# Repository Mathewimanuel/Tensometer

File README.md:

# Tensometer

Stepper-driven ball-screw tensile tester for knit fabrics with embedded conductors, plus ABS and neoprene dog-bones. Teensy 4.1 firmware (`firmware/`) and a Python PC app (`software/`), protocol 0.7 shared by hand between the two.

- `CLAUDE.md`: how Claude Code works on this repo, current status, rules for agents.
- `.claude/skills/tensometer-firmware/SKILL.md`: hardware facts, architecture, safety rules, review checklist.
- `docs/decisions.md`: dated decision log (newest first). `docs/handover.md`: project context. `docs/datasheets/`: manufacturer datasheets.
- `firmware/`: PlatformIO project. Pure logic in `lib/` with native tests, hardware drivers in `src/`.
- `software/`: PySide6 PC app, CLI, and a protocol-level fake firmware (`software/README.md`).
- GitHub issues are the work queue; labels `decision` and `hardware` need Mathew.

## Quick start

Firmware (no hardware needed):

```
pip install platformio
cd firmware
pio test -e native         # unit tests
pio run -e teensy41        # phase 1 firmware
pio run -e teensy41_sim    # phase 1 + simulated continuity module
```

PC app, against the fake firmware:

```
cd software
pip install -e ".[dev]"
pytest -v
tensometer-sim                          # serves a fake Teensy on a TCP socket
python -m tensometer.gui.app            # then connect to socket://127.0.0.1:9000
```

CI runs both: `.github/workflows/firmware.yml` (hook self-test, cppcheck, native tests, both Teensy builds with `-Werror`, memory budget) and `.github/workflows/software.yml` (ruff, pytest).

## Status

Firmware: state machine, motion planner, step ISR, homing sequencer, break-detection classifier, core safety rules, command dispatcher and comms link are implemented and natively tested. Force is fail-closed until the HX711 driver lands (#10), so this build cannot move the motor. Bench bring-up must not be trusted until reset-safe pulls are fitted (#18).

PC app: connect/HELLO with exact protocol-version check, HOME/JOG/ARM/START/STOP, live and cycle plots, per-test CSV logging, review tab.

Flashing the real machine is a manual step with the e-stop in reach; agents are blocked from uploading by `.claude/hooks/block-flash.sh`.

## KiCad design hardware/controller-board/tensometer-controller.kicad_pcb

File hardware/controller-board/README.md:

# Controller board (rev 0.4): reviewed, routed, JLCPCB-ready

Phase 1 controller PCB: Teensy 4.1 socket, TB6600 interface, HX711 cable, limits,
e-stop sense, operator panel, OLED, video-sync LED, and a keyed header for the phase 2
continuity board. **65 x 72 mm** (rev 0.2 was 125 x 88), 2 layers, 1.6 mm, 1 oz, GND
poured on both layers.

Open `tensometer-controller.kicad_pro` in KiCad 10. The files are KiCad 7 format (the
newest KiCad available in the build environment); KiCad 10 opens them and asks to save
in its own format.

| Path | What |
|---|---|
| `tensometer-controller.kicad_sch` / `-schematic.pdf` | Schematic (one A2 sheet, a net label per pin) |
| `tensometer-controller.kicad_pcb` | Routed board (rules below) |
| `jlcpcb/gerbers.zip` | Gerbers + Excellon drill (plated and non-plated holes in separate files) |
| `jlcpcb/BOM.csv`, `jlcpcb/CPL.csv` | JLCPCB assembly BOM and pick-and-place (JLC column format) |
| `renders/` | Routed copper, and the Gerbers rendered back from the zip (gerbv) |
| `tensometer.kicad_sym`, `tensometer.pretty/` | Project library: Teensy 4.1 symbol and socket footprint |
| `tools/` | `design.py` (parts, nets, LCSC numbers, MPNs) and the scripts that rebuild everything: `KRT_DIR=... bash tools/build.sh` |

## What changed in rev 0.4 (independent review + requirements pass)

| Item | Rev 0.3 | Rev 0.4 | Why |
|---|---|---|---|
| 5 V converter U1 | YLPTEC R-78E5.0-1.0, 7-36 V in | **RECOM R-78HB5.0-0.5, 9-72 V in (75 V max)**, 5 V 0.5 A, 3-pin SIP on KiCad's exact footprint | The SMBJ28A TVS only starts conducting at 31 V and clamps at up to ~45 V; a contactor-coil kick could exceed the old converter's 36 V rating. (A TRACO TSR 1-4850WI was tried first; the re-review caught that its vertical version has two extra case pins the footprint lacks.) Not stocked at LCSC: buy from Farnell/RS/Mouser and hand-solder |
| STEP/DIR pull-ups | to the Teensy's +3V3 | to **3V3_PU from U6**, a second TLV75533 on +5V | The Teensy's 3V3 is missing when it is unplugged, not yet up or switched off; STEP/DIR then sat LOW (opto ON) and gave a STEP edge at power-up/unplug, failing bring-up step 2 |
| Input bulk cap | none | **C16 100 uF 50 V** electrolytic on VIN_24 | Damps cable/contactor ringing; a ceramic alone rings |
| F1 | 0.5 A / 30 V PTC | 0.5 A / **60 V** PTC | A tripped PTC holds the full supply voltage; 30 V had no margin over 24 V + transients |
| 24 V tracks | 0.5 mm, 0.2 mm clearance | **1.0 mm** (+24V, 24V_F, VIN_24), **0.5 mm clearance** for the 24 V supply nets (+24V, 24V_F, VIN_24) and **0.3 mm** for the 24 V sense nets (24V_SW, ESTOP_RTN, OPTO_A) | Inrush, fuse-trip and TVS currents; a solder bridge or debris between 24 V and a 3.3 V signal is the failure that kills the Teensy |
| E-stop sense return | J6 pin 2 tied to board GND | **Own net ESTOP_RTN** (J6.2, U5 LED cathode, D5) | The opto now actually isolates. Swapped J6 wires only reverse-bias the LED (D5 carries ~2.4 mA through R11) instead of putting post-contactor 24 V onto GND |
| J10 expansion | Unshrouded 2x8 pins | **Keyed 2x8 box header** (C492443) + **1k in series** on all 9 analog lines (RN5, RN6, R25) + **100R** on SDA/SCL (R26, R27) | A reversed plug put +5 V on an ADC pin; the 1k limits clamp current to ~1.7 mA if the phase 2 board ever drives above 3.3 V |
| Panel buttons | Straight to Teensy pins | **1k in series** from the cable (RN1, RN2, next to J7); 10k pull-ups (RN3, RN4) and 100n at the pin | ESD / miswiring current limit on a cable that leaves the box |
| OLED J8 | 1x4 socket the module plugged into (it could not physically sit there) | **JST-PH 4 cable connector**; mount the OLED on the operator panel | PH (2.0 mm) so it cannot be mated with the HX711's JST-XH 4 by mistake |
| microSD access | J4/J5 cables rose right in front of the Teensy's card slot | Limits and sync LED moved to the right edge; only flat test pads in front of the slot | The firmware logs to SD (skill section 9) |
| Decoupling | C1 14.7 mm from U1, C4 5 mm from U3, C6 6.8 mm from U4 | C1 and C2 directly under U1's pins; C4 beside U3 pin 20; C5/C6 at U4's pins | Reviewer findings |
| Test points | none | TP1-TP7: VIN_24, +5V, +3V3, +3.3VA, ENA_N, 2x GND (bare pads, not assembled) | Bench bring-up step 2 (ENA state with the Teensy in reset) |
| Drill file | PTH and NPTH merged | Separate files | Otherwise JLC may plate the M3 holes |
| Placement rotations | SOT-23, TSSOP only | Also SMDIP-4, resistor arrays, electrolytic (see checklist below) | |
| Silkscreen | DRC ignored silk overlaps | Counted in the routed-board DRC (0 now); connector labels on the board | |
| Board | 57.5 x 72 mm | 65 x 72 mm | Two box headers and a column of cable connectors on the right; still 57% smaller than rev 0.2 |

All of it is **PROPOSED** in `docs/decisions.md`, like the earlier board choices.
Ordering this board effectively approves them, and the firmware skill (section 2.1
still describes the unbuffered wiring) must be updated when they are approved.

## Clearance under the Teensy

The Teensy sits in two 8.5 mm female headers (HC-PM254-8.5H, C41376163). With its own
2.5 mm pin spacer that puts the bottom of the Teensy PCB about **11 mm** above this
board. The tallest parts underneath are D4 (SMA, 2.4 mm max) and the 0603x4 arrays
(0.5 mm); the optional PSRAM/flash chips on the Teensy's underside hang ~1.8 mm, leaving
~7 mm. **Do not solder the Teensy flush** (straight to the board) or use low-profile
sockets: the parts under it would collide. The VUSB-VIN cut is on the Teensy's
underside; do it before plugging it in.

## Layout rules

| Item | Rule | Why |
|---|---|---|
| Signal tracks | 0.25 mm, 0.2 mm clearance | Inside JLC's standard tolerance with margin. IPC-2221 B4 (coated, up to 50 V) needs 0.13 mm |
| 24 V field nets | 0.5 mm clearance to everything for +24V, 24V_F, VIN_24 (net class Field24V); 0.3 mm for 24V_SW, ESTOP_RTN, OPTO_A (Field24VSense) | Margin against bridges/debris, see above. The sense nets carry a few mA behind R11, and 0.5 mm on all six nets would not route on this board; 0.3 mm is still above IPC-2221 B4 (0.13 mm up to 50 V) |
| Power tracks | 1.0 mm: +24V, 24V_F, VIN_24; 0.5 mm: +5V, VIN_T, GND; 0.4 mm: +3.3VA, 24V_SW, ESTOP_RTN; 0.25 mm: +3V3 | IPC-2221, 1 oz, 10 C rise: 1.0 mm ~2.5 A, 0.5 mm ~1.5 A, 0.25 mm ~0.8 A. The 5 V rail is under 0.5 A; +3V3 only feeds pull-ups, the OLED, the panel LED and phase 2 logic |
| Vias | 0.6 mm pad / 0.3 mm drill, tented | JLC standard, no surcharge |
| Via-in-pad | None | Unfilled vias wick solder |
| GND | Pour on both layers, 0.3 mm clearance, thermal reliefs (0.5 mm spokes), islands removed; stitching vias on a 5 mm grid plus a ring 1.6 mm in from the edge; a dedicated via at every two-pad SMD GND pad; stitching vias that would only tie floating pour scraps together are removed | One low-impedance ground; decoupling caps get the shortest return; no floating copper |
| Edge | Copper 0.5 mm from the board edge | |
| Fiducials | 3 (1 mm copper, 2 mm mask opening) | For the SMT line |

Tracks neck down to the pad width where they enter a small pad (a fraction of a mm).

## Phase 2 expansion (J10): how it ties in

J10 is the only link to the future continuity/routing board (firmware skill sections
2.4-2.5). Pin 1 = ADC_A0 ... pin 8 = ADC_B3 (each through 1k to Teensy pins 16, 17, 20,
21, 22, 23, 24, 25), pin 9 = V_EXC_SENSE (1k to pin 26), 10/15/16 = GND, 11/12 = I2C
SDA/SCL (via 100R; shared with the OLED, 4k7 pull-ups on this board), 13 = +3V3, 14 = +5V.

- The phase 2 board does all its own analog: precision V_EXC supply, reference
  resistors, analog switches, instrumentation amps, clamps. This board only carries the
  finished 0-3.3 V signals to the ADC pins.
- Relays (via MCP23017 + ULN2803 on the phase 2 board) are driven over the shared I2C.
  The MCP23017 must run at 3.3 V (the bus pull-ups go to +3V3).
- Power budget: +5V comes from the 0.5 A R-78HB. This board uses ~0.25 A (Teensy, opto
  drive, sync LED, HX711 LDO), leaving ~0.25 A for phase 2: relays (at most two
  energised), V_EXC regulator, amps. That is enough for signal relays, but if phase 2
  needs more it should take its own supply. Total capacitance on +5V must stay under
  100 uF (converter limit for a normal start-up); this board has ~35 uF plus the Teensy's own input capacitance. +3V3 comes from the Teensy's ~250 mA regulator, which already
  feeds pull-ups, the OLED and the panel: phase 2 should use it for logic levels only and
  make its own 3.3 V for anything else.
- No phase 2 board plugged in: the ADC pins float through 1k; the firmware treats the
  continuity module as absent (module presence check, skill section 1.2).

## Checks done

- Schematic: the netlist KiCad exports matches `design.py` exactly (68 nets, 81 parts).
- PCB: every pad carries the schematic's net; footprints linked to symbols by UUID.
- KiCad DRC on the routed board, silkscreen included, with the 0.5 mm 24 V class: **0 errors, 0 unconnected**. Left: library warnings that only appear because this machine has no global KiCad library table.
- Separate GND check: every GND pad, track, via and pour fragment is one connected copper island.
- Mask Gerber has no openings at vias (tented).
- Gerbers rendered back with gerbv: outline, copper, drills and silk as expected.
- kicad-happy (github.com/aklofas/kicad-happy) analyzers and an independent reviewer agent on rev 0.3 and again on rev 0.4 (results in `docs/decisions.md`).
- Every LCSC number checked against the JLC parts database (jlcparts snapshot; stock fetched 2026-09-15..10-28, so re-check stock when ordering). U1 (R-78HB5.0-0.5) is not stocked at LCSC: Farnell, RS and Mouser carry it.
- Not done: ERC (no CLI ERC in KiCad 7), a 3D model fit check, SPICE.

## Ordering at JLCPCB

1. PCB: upload `jlcpcb/gerbers.zip`. 2 layers, 1.6 mm, 1 oz, any colour/finish.
2. Assembly: top side. Upload `BOM.csv` and `CPL.csv`.
3. **Check every polarised part in JLC's placement preview** before paying (table below). A diode or IC rotated 180 degrees still fits its pads, so the preview is the only check. D2 backwards shorts 24 V and trips F1; U3 backwards dies.
4. Cheapest route: let JLC place only the SMD parts and hand-solder the through-hole ones (U1 and all connectors): untick those BOM lines (U1 must be bought separately anyway). Each extended part carries JLC's extended-part fee.
5. Not on the BOM: the Teensy itself; 2x 1x24 female headers for its socket (C41376163, hand-solder); the J2 mating plug (C440884); test points (bare pads).

| Part | What the preview must show (board viewed from the top, USB edge up) |
|---|---|
| D1 SS34 | Cathode band on the **right** |
| D2 SMBJ28A | Cathode band at the **bottom** (towards U3) |
| D3 LED, D4 SS14, D5 1N4148W | Cathode mark on the **left** |
| Q1 AO3400A, U4 TLV75533 | Pin 1 at the **top-left** (two pins on the left for Q1, three for U4) |
| U3 74AHCT244 | Pin 1 dot at the **top-left** |
| U5 LTV-817S | Pin 1 dot at the **top-left** (its rotation is the least certain; see `gen_fab.py`) |
| C16 electrolytic | **+** at the **bottom** |
| RN1-RN6 arrays | Not polarised, but must sit square on the 8 pads |

## Before power-up

- **Cut the Teensy's VUSB-VIN pad**; the board feeds VIN through D4.
- Bench bring-up step 2 (firmware skill section 13): with the Teensy held in reset, ENA_N (TP5) must sit at the level that keeps the TB6600 disabled.
- Known, by TB6600 design: a broken ENA wire or a dead +5 V rail leaves the driver **enabled** (no step pulses, so it holds position). The contactor/e-stop is what removes motor power.
- +5V and +3V3 leave the box unfused on J7, J9 and J10. A shorted cable takes the rail down (and with it the ENA opto, see above). Acceptable for a bench machine with an e-stop; add PTCs on the cables if that changes.
- Run the I2C bus at 100 kHz: the OLED is now on a cable and phase 2 adds more.
- JLC may want panel rails because parts sit close to the edges; check when quoting.

## Design choices awaiting Mathew's OK (docs/decisions.md)

1. 74AHCT244 buffer between Teensy and TB6600 (3.3 V vs 5 V, 10 mA pin limit, reset back-feed); 10k reset-safe pulls at its inputs (issue #18).
2. E-stop sense via LTV-817S with an isolated return: LOW = 24 V present after the contactor, HIGH = e-stop pressed or wire broken.
3. Board logic powered from 24 V **before** the contactor (J1); J6 senses the contactor output.
4. HX711 off-board on the carriage, own TLV75533 LDO.
5. Rev 0.4 changes in the table above.

## Unverified, check against datasheets

- LTV-817S land pattern: uses KiCad's `SMDIP-4_W9.53mm` (standard gull-wing DIP-4).
- R-78HB5.0-0.5: pinout 1 +Vin, 2 GND, 3 +Vout, 9-72 V in, 0.5 A, 11.5 x 8.5 x 17.5 mm (RECOM datasheet); KiCad's footprint for exactly this part. Buy the vertical (non-"L") version.
- 0603x4 arrays use KiCad's convex footprint; UNI-ROYAL 4D03 is the convex type (TODO(verify) against its datasheet).
- KF2EDGR-5.08-6P and WJ500V-5.08-2P use Phoenix footprints with the same 5.08 mm pitch; body outlines differ slightly from the silkscreen.

## Connector map

| Ref | Connector | Pins |
|---|---|---|
| J1 | 5.08 mm screw, 2 | +24 V (before contactor), 0 V |
| J2 | 5.08 mm pluggable, 6 | PUL+ PUL- DIR+ DIR- ENA+ ENA- (to TB6600; the + terminals are 5 V) |
| J3 | JST-XH 4 | 3V3A, GND, DOUT, SCK (to the HX711 module) |
| J4 / J5 | JST-XH 2 | LIM_NEAR / LIM_FAR: NC switch to GND (labelled on the board) |
| J6 | 5.08 mm screw, 2 | 24 V after the contactor, that supply's 0 V (isolated from board GND by the opto) |
| J7 | IDC 2x5 box | START, STOP, JOG+, JOG-, HOME, TARE, FAULT LED (330 R on board), 3V3, GND, GND |
| J8 | JST-PH 4 | OLED: GND, 3V3, SCL, SDA |
| J9 | JST-XH 2 | Sync LED: +5 V, LED cathode (100 R on board, ~20 mA) |
| J10 | IDC 2x8 box, keyed | Phase 2: ADC_A0-3, ADC_B0-3, V_EXC_SENSE (all via 1k), GND, I2C (via 100R), 3V3, 5V, GND, GND. The phase 2 board's cable must use the same notch-to-pin-1 convention |

## How it was routed

`tools/route_board.py` drives [KiCad Routing Tools](https://github.com/drandyhaas/KiCadRoutingTools)
(MIT, commit 6ae347ba): a GND plane on B.Cu, then every net at the widths above with
B.Cu made costly so the plane stays whole. The router writes KiCad 9 syntax; the script
converts it to KiCad 7, pours GND on F.Cu, fills, drops stitching vias where both pours
are solid (and into any walled-in pour fragment), refills with island removal, removes
stitching vias that only join floating scraps, and refills again. On a board this dense
the router's result swings with its settings, so the script retries a short list of
them until KiCad's DRC reports zero unconnected items. `tools/build.sh` fails if the
final DRC has any error.

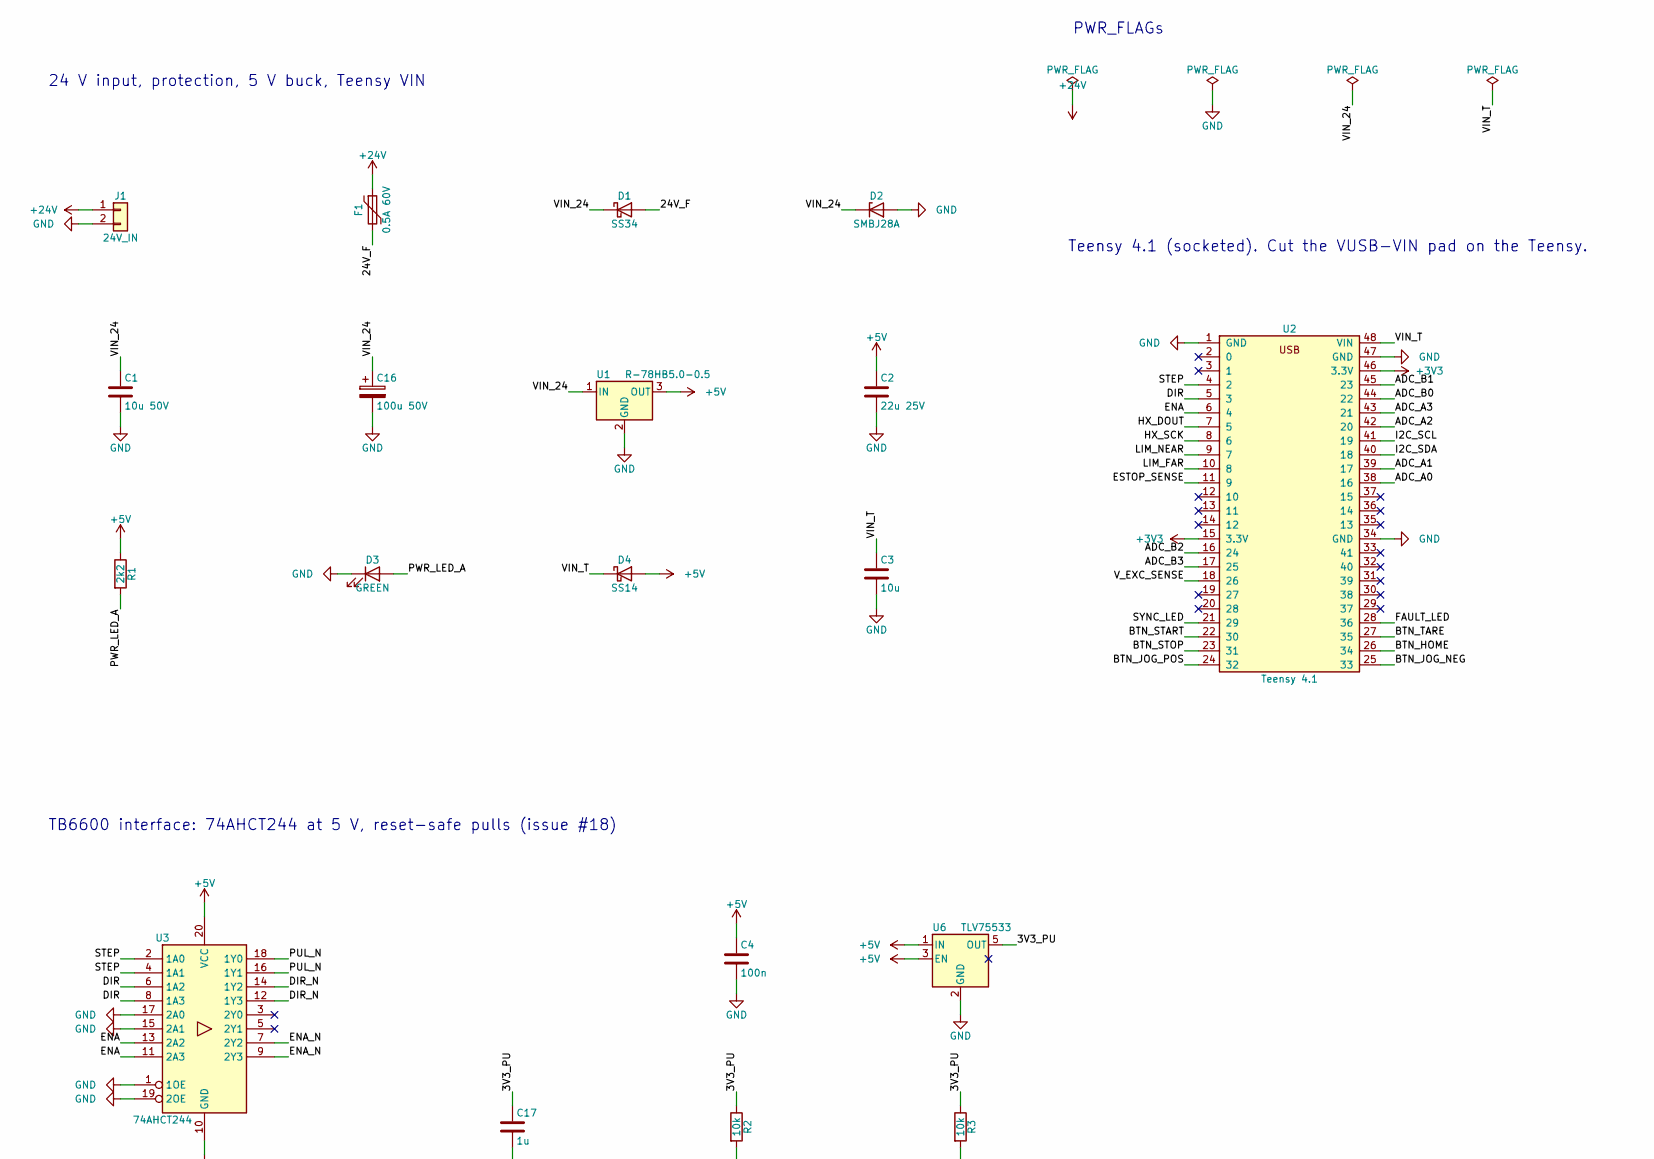
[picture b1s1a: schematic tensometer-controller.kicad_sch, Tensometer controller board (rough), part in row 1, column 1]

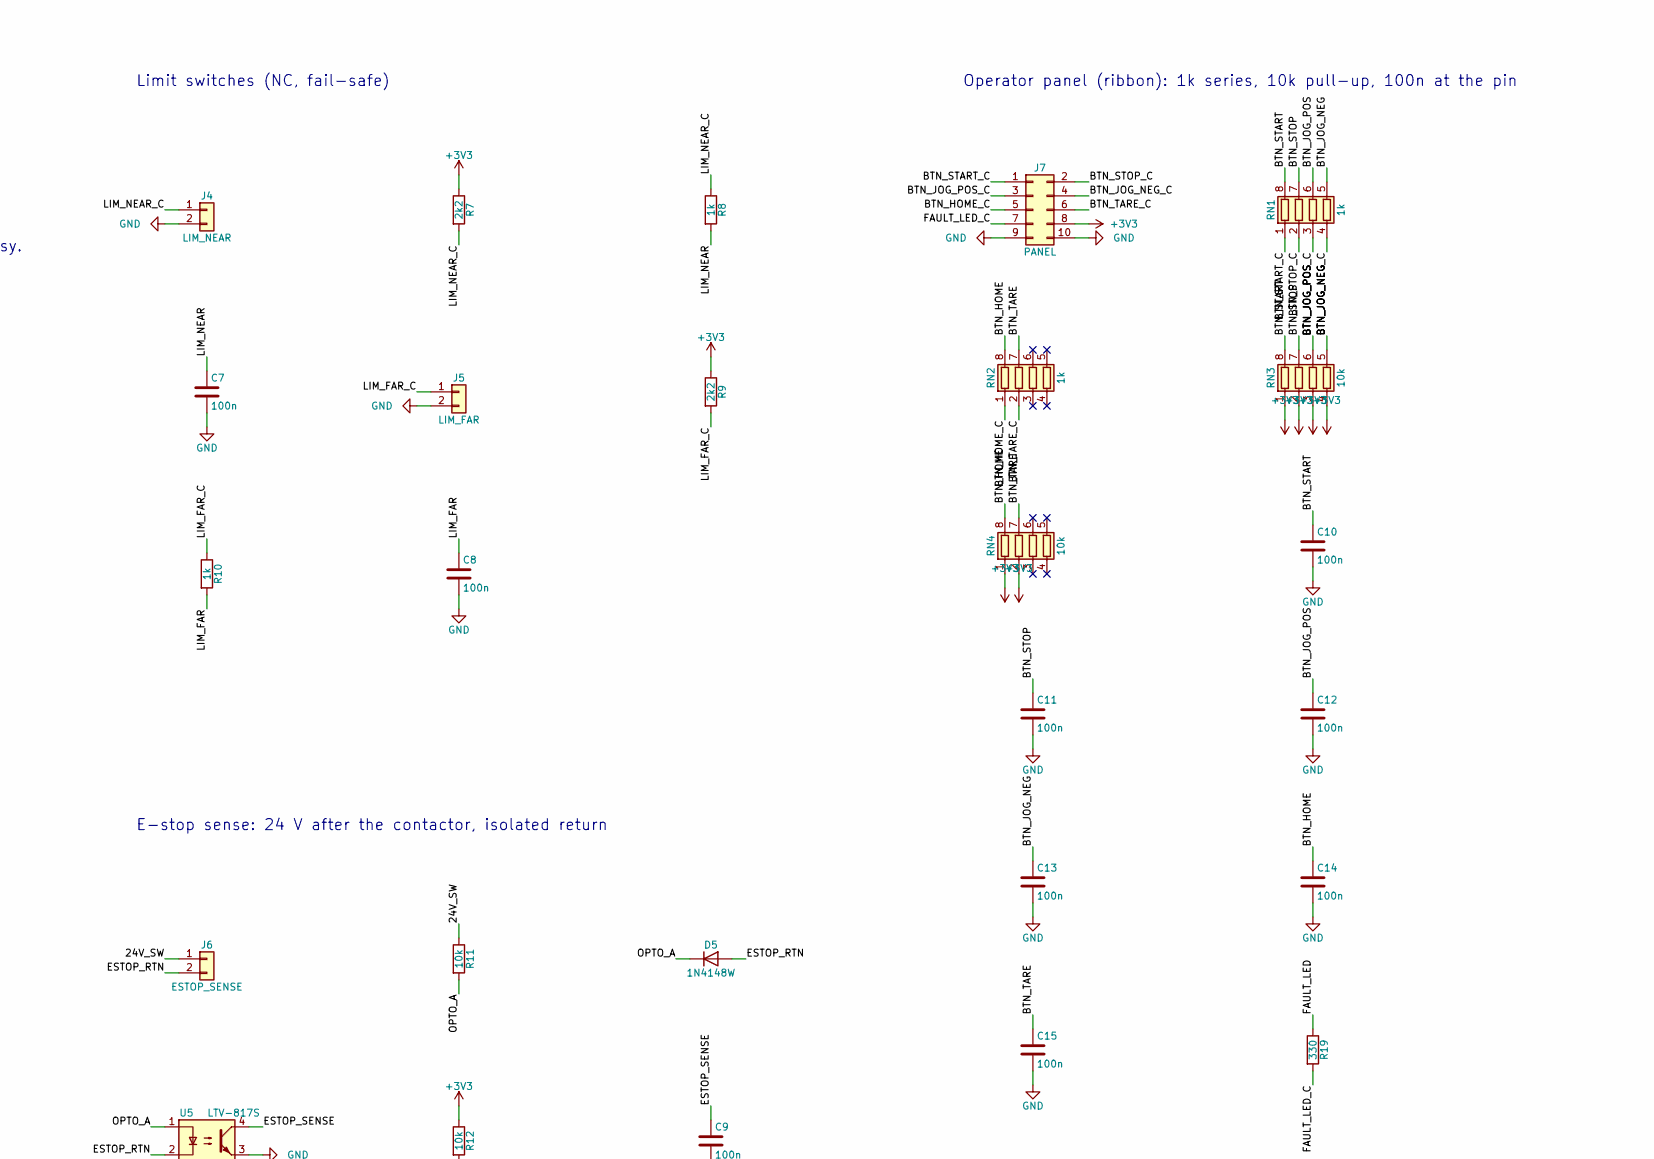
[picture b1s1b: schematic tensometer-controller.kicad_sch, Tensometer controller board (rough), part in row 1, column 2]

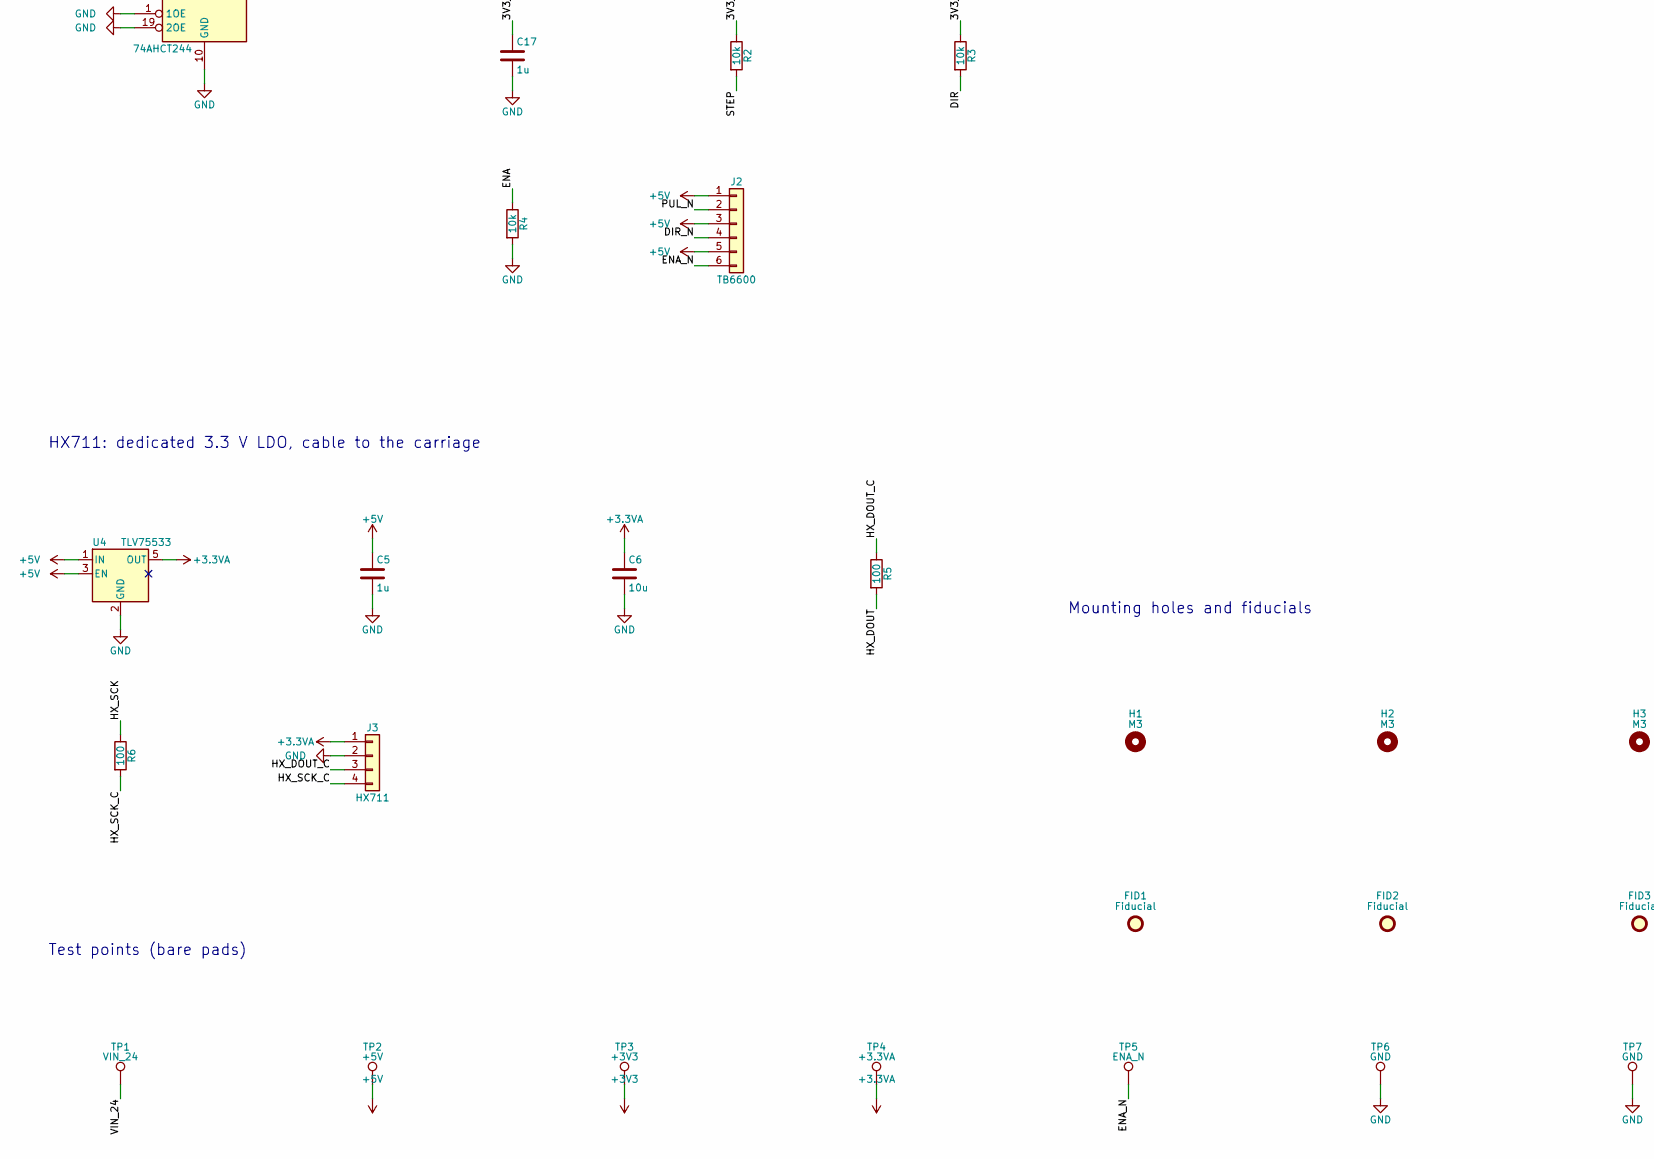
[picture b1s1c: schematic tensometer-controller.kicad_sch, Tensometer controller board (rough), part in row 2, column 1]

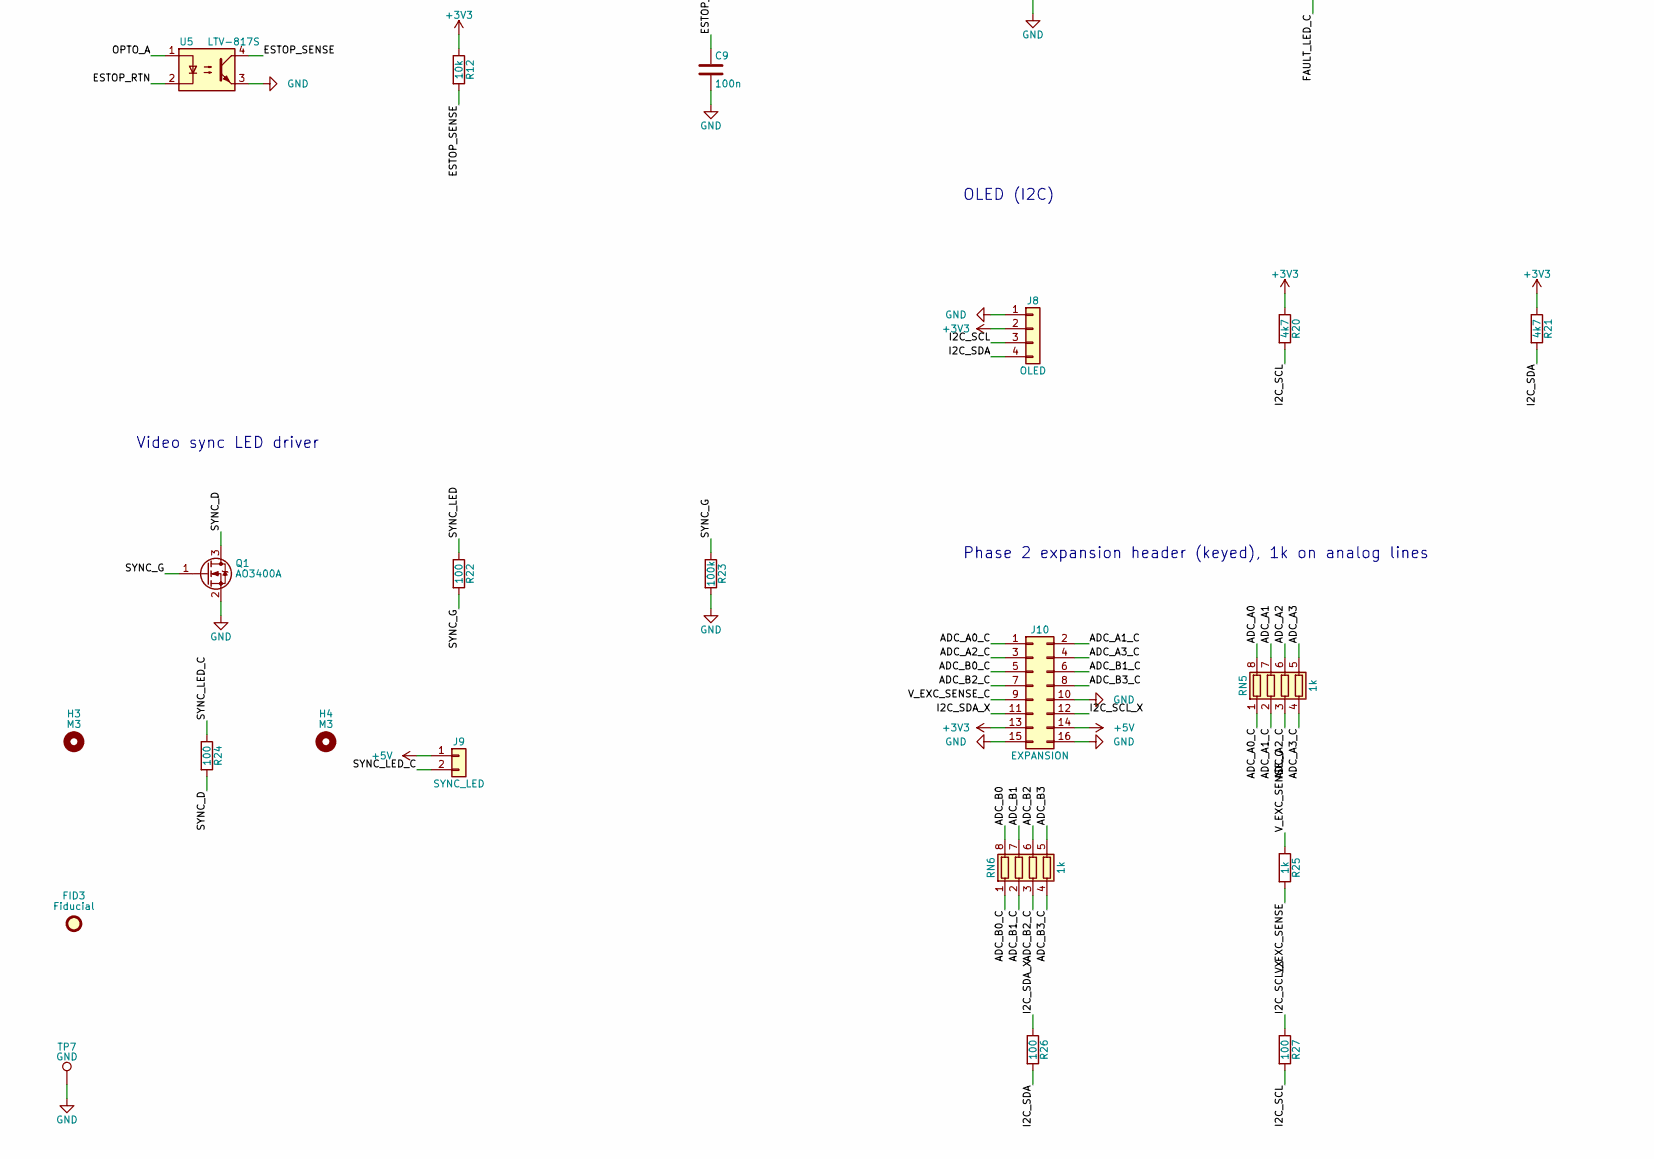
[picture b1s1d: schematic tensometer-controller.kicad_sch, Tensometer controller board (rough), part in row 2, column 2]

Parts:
C1: 10u 50V; C_1206_3216Metric; MPN CL31A106KBHNNNE; LCSC C13585
C2: 22u 25V; C_0805_2012Metric; MPN CL21A226MAQNNNE; LCSC C45783
C3, C6: 10u; C_0805_2012Metric; MPN CL21A106KAYNNNE; LCSC C15850
C4, C7, C8, C9, C10, C11, C12, C13, C14, C15: 100n; C_0805_2012Metric; MPN CC0805KRX7R9BB104; LCSC C49678
C5, C17: 1u; C_0805_2012Metric; MPN CL21B105KBFNNNE; LCSC C28323
C16: 100u 50V; CP_Elec_6.3x7.7; MPN RVT50V100M6X8; LCSC C47023117
D1: SS34; D_SMA; MPN SS34; LCSC C8678
D2: SMBJ28A; D_SMB; MPN SMBJ28A; LCSC C113997
D3: GREEN; LED_0805_2012Metric; MPN KT-0805G; LCSC C2297
D4: SS14; D_SMA; MPN SS14; LCSC C2480
D5: 1N4148W; D_SOD-123; MPN 1N4148W; LCSC C81598
F1: 0.5A 60V; Fuse_1812_4532Metric; MPN 1812L050/60GR; LCSC C19078719
FID1, FID2, FID3: Fiducial; Fiducial_1mm_Mask2mm
H1, H2, H3, H4: M3; MountingHole_3.2mm_M3
J1: 24V_IN; TerminalBlock_Phoenix_MKDS-1,5-2-5.08_1x02_P5.08mm_Horizont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; MPN WJ500V-5.08-2P; LCSC C8465
J2: TB6600; PhoenixContact_MSTBA_2,5_6-G-5,08_1x06_P5.08mm_Horizontal; MPN KF2EDGR-5.08-6P; LCSC C441208
J3: HX711; JST_XH_B4B-XH-A_1x04_P2.50mm_Vertical; MPN B4B-XH-A(LF)(SN); LCSC C144395
J4: LIM_NEAR; JST_XH_B2B-XH-A_1x02_P2.50mm_Vertical; MPN B2B-XH-A(LF)(SN); LCSC C158012
J5: LIM_FAR; JST_XH_B2B-XH-A_1x02_P2.50mm_Vertical; MPN B2B-XH-A(LF)(SN); LCSC C158012
J6: ESTOP_SENSE; TerminalBlock_Phoenix_MKDS-1,5-2-5.08_1x02_P5.08mm_Horizont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; MPN WJ500V-5.08-2P; LCSC C8465
J7: PANEL; IDC-Header_2x05_P2.54mm_Vertical; MPN 2.54-2*5P简牛; LCSC C5665
J8: OLED; JST_PH_B4B-PH-K_1x04_P2.00mm_Vertical; MPN B4B-PH-K-S(LF)(SN); LCSC C131334
J9: SYNC_LED; JST_XH_B2B-XH-A_1x02_P2.50mm_Vertical; MPN B2B-XH-A(LF)(SN); LCSC C158012
J10: EXPANSION; IDC-Header_2x08_P2.54mm_Vertical; MPN BH254V-16P; LCSC C492443
Q1: AO3400A; SOT-23; MPN AO3400A; LCSC C20917
R1, R7, R9: 2k2; R_0805_2012Metric; MPN 0805W8F2201T5E; LCSC C17520
R2, R3, R4, R12: 10k; R_0805_2012Metric; MPN 0805W8F1002T5E; LCSC C17414
R5, R6, R22, R24, R26, R27: 100; R_0805_2012Metric; MPN 0805W8F1000T5E; LCSC C17408
R8, R10, R25: 1k; R_0805_2012Metric; MPN 0805W8F1001T5E; LCSC C17513
R11: 10k; R_1206_3216Metric; MPN 1206W4F1002T5E; LCSC C17902
R19: 330; R_0805_2012Metric; MPN 0805W8F3300T5E; LCSC C17630
R20, R21: 4k7; R_0805_2012Metric; MPN 0805W8F4701T5E; LCSC C17673
R23: 100k; R_0805_2012Metric; MPN 0805W8F1003T5E; LCSC C149504
RN1, RN2, RN5, RN6: 1k; R_Array_Convex_4x0603; MPN 4D03WGJ0102T5E; LCSC C20197
RN3, RN4: 10k; R_Array_Convex_4x0603; MPN 4D03WGJ0103T5E; LCSC C29718
TP1: VIN_24; TestPoint_Pad_D1.5mm
TP2: +5V; TestPoint_Pad_D1.5mm
TP3: +3V3; TestPoint_Pad_D1.5mm
TP4: +3.3VA; TestPoint_Pad_D1.5mm
TP5: ENA_N; TestPoint_Pad_D1.5mm
TP6, TP7: GND; TestPoint_Pad_D1.5mm
U1: R-78HB5.0-0.5; Converter_DCDC_RECOM_R-78HB-0.5_THT; MPN R-78HB5.0-0.5; LCSC C7333563
U2: Teensy 4.1; Teensy41_Socket; MPN TEENSY41
U3: 74AHCT244; TSSOP-20_4.4x6.5mm_P0.65mm; MPN 74AHCT244PW,118; LCSC C135583
U4, U6: TLV75533; SOT-23-5; MPN TLV75533PDBVR; LCSC C404027
U5: LTV-817S; SMDIP-4_W9.53mm; MPN LTV-817S-TA1-C; LCSC C109227

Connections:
+3.3VA: C6.1, J3.1, TP4.1, U4.5 (OUT)
+3V3: J7.8, J8.2, J10.13, R7.1, R9.1, R12.1, R20.1, R21.1, RN3.1 (R1.1), RN3.2 (R2.1), RN3.3 (R3.1), RN3.4 (R4.1), RN4.1 (R1.1), RN4.2 (R2.1), TP3.1, U2.15 (3.3V), U2.46 (3.3V)
+5V: C2.1, C4.1, C5.1, D4.2 (A), J2.1, J2.3, J2.5, J9.1, J10.14, R1.1, TP2.1, U1.3 (OUT), U3.20 (VCC), U4.1 (IN), U4.3 (EN), U6.1 (IN), U6.3 (EN)
+24V: F1.1, J1.1
/3V3_PU: C17.1, R2.1, R3.1, U6.5 (OUT)
/24V_F: D1.2 (A), F1.2
/24V_SW: J6.1, R11.1
/ADC_A0: RN5.8 (R1.2), U2.38 (16)
/ADC_A0_C: J10.1, RN5.1 (R1.1)
/ADC_A1: RN5.7 (R2.2), U2.39 (17)
/ADC_A1_C: J10.2, RN5.2 (R2.1)
/ADC_A2: RN5.6 (R3.2), U2.42 (20)
/ADC_A2_C: J10.3, RN5.3 (R3.1)
/ADC_A3: RN5.5 (R4.2), U2.43 (21)
/ADC_A3_C: J10.4, RN5.4 (R4.1)
/ADC_B0: RN6.8 (R1.2), U2.44 (22)
/ADC_B0_C: J10.5, RN6.1 (R1.1)
/ADC_B1: RN6.7 (R2.2), U2.45 (23)
/ADC_B1_C: J10.6, RN6.2 (R2.1)
/ADC_B2: RN6.6 (R3.2), U2.16 (24)
/ADC_B2_C: J10.7, RN6.3 (R3.1)
/ADC_B3: RN6.5 (R4.2), U2.17 (25)
/ADC_B3_C: J10.8, RN6.4 (R4.1)
/BTN_HOME: C14.1, RN2.8 (R1.2), RN4.8 (R1.2), U2.26 (34)
/BTN_HOME_C: J7.5, RN2.1 (R1.1)
/BTN_JOG_NEG: C13.1, RN1.5 (R4.2), RN3.5 (R4.2), U2.25 (33)
/BTN_JOG_NEG_C: J7.4, RN1.4 (R4.1)
/BTN_JOG_POS: C12.1, RN1.6 (R3.2), RN3.6 (R3.2), U2.24 (32)
/BTN_JOG_POS_C: J7.3, RN1.3 (R3.1)
/BTN_START: C10.1, RN1.8 (R1.2), RN3.8 (R1.2), U2.22 (30)
/BTN_START_C: J7.1, RN1.1 (R1.1)
/BTN_STOP: C11.1, RN1.7 (R2.2), RN3.7 (R2.2), U2.23 (31)
/BTN_STOP_C: J7.2, RN1.2 (R2.1)
/BTN_TARE: C15.1, RN2.7 (R2.2), RN4.7 (R2.2), U2.27 (35)
/BTN_TARE_C: J7.6, RN2.2 (R2.1)
/DIR: R3.2, U2.5 (3), U3.6 (1A2), U3.8 (1A3)
/DIR_N: J2.4, U3.12 (1Y3), U3.14 (1Y2)
/ENA: R4.1, U2.6 (4), U3.11 (2A3), U3.13 (2A2)
/ENA_N: J2.6, TP5.1, U3.7 (2Y2), U3.9 (2Y3)
/ESTOP_RTN: D5.2 (A), J6.2, U5.2
/ESTOP_SENSE: C9.1, R12.2, U2.11 (9), U5.4
/FAULT_LED: R19.1, U2.28 (36)
/FAULT_LED_C: J7.7, R19.2
/HX_DOUT: R5.2, U2.7 (5)
/HX_DOUT_C: J3.3, R5.1
/HX_SCK: R6.1, U2.8 (6)
/HX_SCK_C: J3.4, R6.2
/I2C_SCL: J8.3, R20.2, R27.2, U2.41 (19)
/I2C_SCL_X: J10.12, R27.1
/I2C_SDA: J8.4, R21.2, R26.2, U2.40 (18)
/I2C_SDA_X: J10.11, R26.1
/LIM_FAR: C8.1, R10.2, U2.10 (8)
/LIM_FAR_C: J5.1, R9.2, R10.1
/LIM_NEAR: C7.1, R8.2, U2.9 (7)
/LIM_NEAR_C: J4.1, R7.2, R8.1
/OPTO_A: D5.1 (K), R11.2, U5.1
/PUL_N: J2.2, U3.16 (1Y1), U3.18 (1Y0)
/PWR_LED_A: D3.2 (A), R1.2
/STEP: R2.2, U2.4 (2), U3.2 (1A0), U3.4 (1A1)
/SYNC_D: Q1.3 (D), R24.2
/SYNC_G: Q1.1 (G), R22.2, R23.1
/SYNC_LED: R22.1, U2.21 (29)
/SYNC_LED_C: J9.2, R24.1
/VIN_24: C1.1, C16.1, D1.1 (K), D2.1 (K), TP1.1, U1.1 (IN)
/VIN_T: C3.1, D4.1 (K), U2.48 (VIN)
/V_EXC_SENSE: R25.2, U2.18 (26)
/V_EXC_SENSE_C: J10.9, R25.1
GND: C1.2, C2.2, C3.2, C4.2, C5.2, C6.2, C7.2, C8.2, C9.2, C10.2, C11.2, C12.2, C13.2, C14.2, C15.2, C16.2, C17.2, D2.2 (A), D3.1 (K), J1.2, J3.2, J4.2, J5.2, J7.9, J7.10, J8.1, J10.10, J10.15, J10.16, Q1.2 (S), R4.2, R23.2, TP6.1, TP7.1, U1.2 (GND), U2.1 (GND), U2.34 (GND), U2.47 (GND), U3.1 (1OE), U3.10 (GND), U3.15 (2A1), U3.17 (2A0), U3.19 (2OE), U4.2 (GND), U5.3, U6.2 (GND)

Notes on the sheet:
24 V input, protection, 5 V buck, Teensy VIN
Teensy 4.1 (socketed). Cut the VUSB-VIN pad on the Teensy.
TB6600 interface: 74AHCT244 at 5 V, reset-safe pulls (issue #18)
HX711: dedicated 3.3 V LDO, cable to the carriage
Limit switches (NC, fail-safe)
E-stop sense: 24 V after the contactor, isolated return
Operator panel (ribbon): 1k series, 10k pull-up, 100n at the pin
OLED (I2C)
Video sync LED driver
Phase 2 expansion header (keyed), 1k on analog lines
Test points (bare pads)
Mounting holes and fiducials
PWR_FLAGs

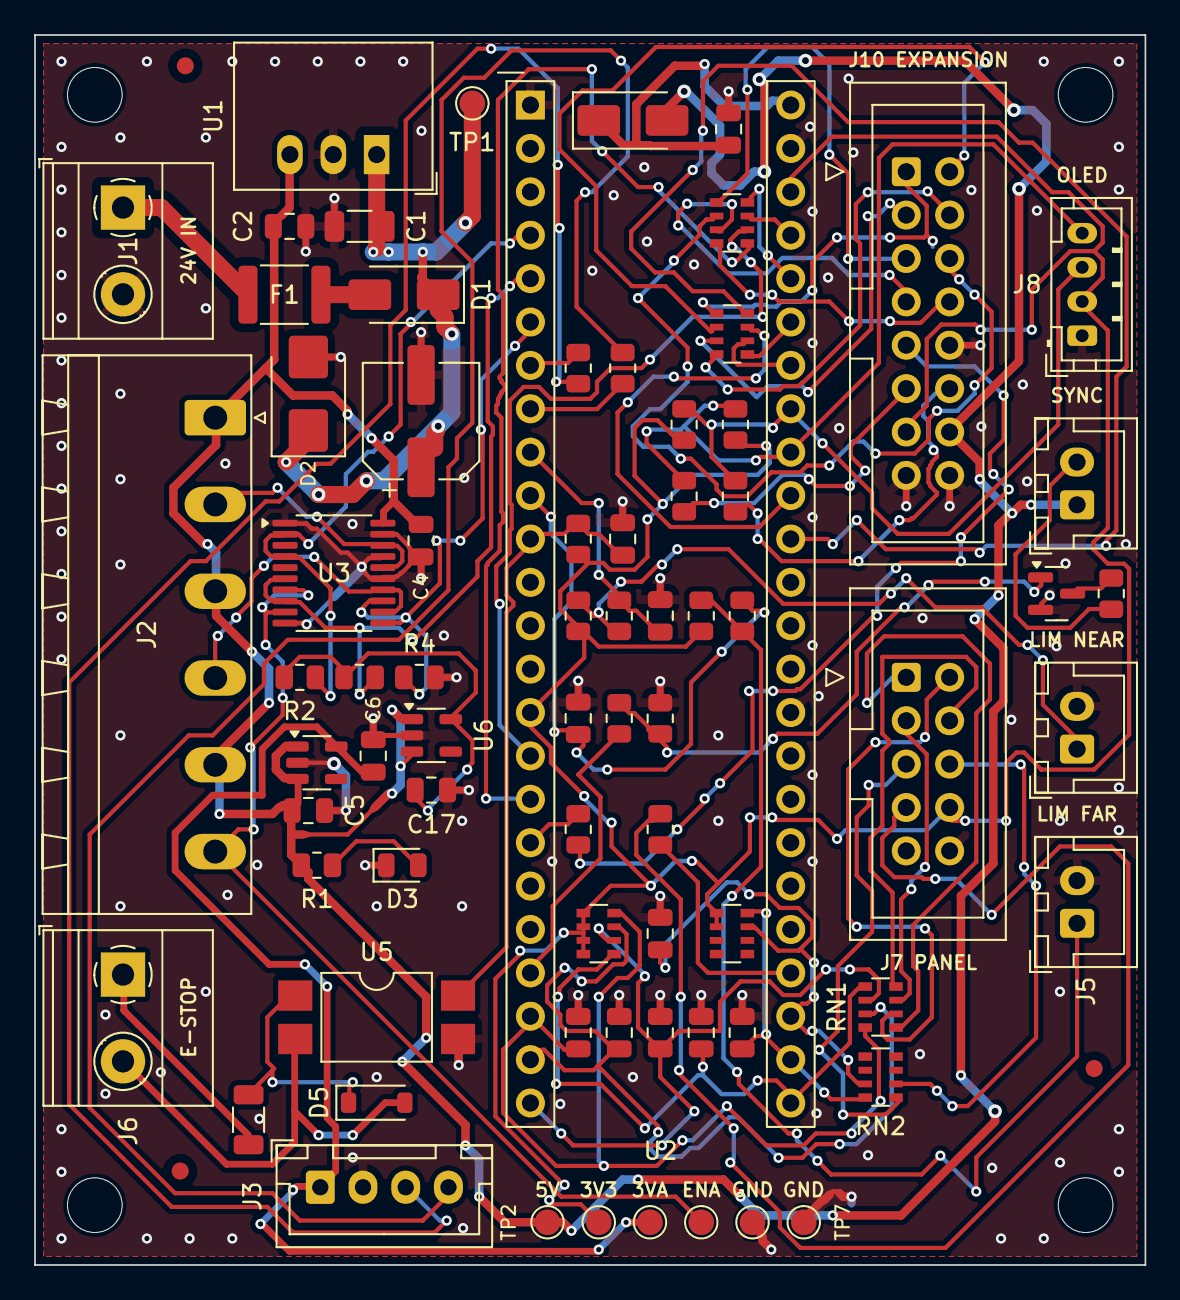
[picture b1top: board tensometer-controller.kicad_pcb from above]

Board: 2 copper layers, 65.0 x 72.0 mm, 81 parts (0 on the bottom side), 68 nets.

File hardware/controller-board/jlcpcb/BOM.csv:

Comment,Designator,Footprint,LCSC Part #
10u 50V,C1,C_1206_3216Metric,C13585
22u 25V,C2,C_0805_2012Metric,C45783
10u,"C3,C6",C_0805_2012Metric,C15850
100n,"C4,C7,C8,C9,C10,C11,C12,C13,C14,C15",C_0805_2012Metric,C49678
1u,"C5,C17",C_0805_2012Metric,C28323
100u 50V,C16,CP_Elec_6.3x7.7,C47023117
SS34,D1,D_SMA,C8678
SMBJ28A,D2,D_SMB,C113997
GREEN,D3,LED_0805_2012Metric,C2297
SS14,D4,D_SMA,C2480
1N4148W,D5,D_SOD-123,C81598
0.5A 60V,F1,Fuse_1812_4532Metric,C19078719
24V_IN,J1,"TerminalBlock_Phoenix_MKDS-1,5-2-5.08_1x02_P5.08mm_Horizontal",C8465
TB6600,J2,"PhoenixContact_MSTBA_2,5_6-G-5,08_1x06_P5.08mm_Horizontal",C441208
HX711,J3,JST_XH_B4B-XH-A_1x04_P2.50mm_Vertical,C144395
LIM_NEAR,J4,JST_XH_B2B-XH-A_1x02_P2.50mm_Vertical,C158012
LIM_FAR,J5,JST_XH_B2B-XH-A_1x02_P2.50mm_Vertical,C158012
ESTOP_SENSE,J6,"TerminalBlock_Phoenix_MKDS-1,5-2-5.08_1x02_P5.08mm_Horizontal",C8465
PANEL,J7,IDC-Header_2x05_P2.54mm_Vertical,C5665
OLED,J8,JST_PH_B4B-PH-K_1x04_P2.00mm_Vertical,C131334
SYNC_LED,J9,JST_XH_B2B-XH-A_1x02_P2.50mm_Vertical,C158012
EXPANSION,J10,IDC-Header_2x08_P2.54mm_Vertical,C492443
AO3400A,Q1,SOT-23,C20917
2k2,"R1,R7,R9",R_0805_2012Metric,C17520
10k,"R2,R3,R4,R12",R_0805_2012Metric,C17414
100,"R5,R6,R22,R24,R26,R27",R_0805_2012Metric,C17408
1k,"R8,R10,R25",R_0805_2012Metric,C17513
10k,R11,R_1206_3216Metric,C17902
330,R19,R_0805_2012Metric,C17630
4k7,"R20,R21",R_0805_2012Metric,C17673
100k,R23,R_0805_2012Metric,C149504
1k,"RN1,RN2,RN5,RN6",R_Array_Convex_4x0603,C20197
10k,"RN3,RN4",R_Array_Convex_4x0603,C29718
R-78HB5.0-0.5,U1,Converter_DCDC_RECOM_R-78HB-0.5_THT,C7333563
74AHCT244,U3,TSSOP-20_4.4x6.5mm_P0.65mm,C135583
TLV75533,"U4,U6",SOT-23-5,C404027
LTV-817S,U5,SMDIP-4_W9.53mm,C109227

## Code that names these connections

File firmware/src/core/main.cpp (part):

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// the explicit write documents intent.
//
// SAFETY GAP (confirmed 2026-10-26, skill 2.1): there is no 74AHCT244 buffer and no
// pull-down resistor anywhere on ENA (nor pull-ups on STEP/DIR) -- the Teensy pins
// wire straight to the TB6600's common-anode (+5V) opto inputs. Nothing holds ENA
// disabled between power-up and this line running, or during a reset while the 5V/
// TB6600 side stays powered. This code cannot close that gap; it needs a physical
// pull-down added on the ENA line (see docs/decisions.md 2026-10-26, issue #18).
void drive_outputs_safe() {
    pinMode(cfg::pin::ENA, OUTPUT);
    digitalWriteFast(cfg::pin::ENA, LOW);

    // STEP idles HIGH (opto off). pinMode(OUTPUT) briefly drives LOW for well under
    // 1 us before the write below: shorter than any opto's minimum pulse, and the
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
void configure_inputs() {
    // Limits and e-stop use external pull-ups and RC filters (skill 2.6): plain INPUT.
    pinMode(cfg::pin::LIM_NEAR, INPUT);
    pinMode(cfg::pin::LIM_FAR, INPUT);
    pinMode(cfg::pin::ESTOP_SENSE, INPUT);
    pinMode(cfg::pin::HX711_DOUT, INPUT);
    pinMode(cfg::pin::HX711_SCK, OUTPUT);
    digitalWriteFast(cfg::pin::HX711_SCK, LOW);  // SCK high > 60 us powers the HX711 down
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    // NC switches to GND with external pull-ups (skill 2.6): open/tripped or a broken wire
    // reads HIGH. TODO(verify) wiring polarity on the bench. Polled here, not the
    // pin-change ISR skill 3.2 requires: acceptable only while no motion is possible.
    in.lim_near_active = digitalReadFast(cfg::pin::LIM_NEAR) == HIGH;
    in.lim_far_active = digitalReadFast(cfg::pin::LIM_FAR) == HIGH;
    // STUB / TODO(verify): ESTOP_SENSE opto output polarity is not documented anywhere, so
    // it is not read. Must be resolved (with the pin-change ISR) before any motion exists.
    in.estop_active = false;
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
